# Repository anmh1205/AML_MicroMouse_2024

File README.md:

# AML MicroMouse 2024

A Micromouse robotics development repository combining STM32-based firmware variants, maze-solving algorithms, hardware design, simulation, and engineering records from the 2024 project.

## Project overview

Micromouse is a robotics challenge that combines mapping an unknown maze with planning and accurately driving a route to the destination. The 2024 project explores both sides of that problem: embedded-control software for the physical robot and software tools for developing and testing maze-solving behavior.

Unlike a single-board firmware example, this repository preserves **multiple hardware and firmware variants**, development experiments, technical references, and documentation. A directory name may refer to an earlier board revision rather than the final target.

## What is included

| Area | Examples found in the repository |
| --- | --- |
| Embedded firmware | STM32 projects, startup files, HAL drivers, MCU configurations |
| MCU variants | STM32F407-related projects and an STM32H743-based all-in-one board project |
| Real-time software | FreeRTOS experiments and related MCU project material |
| Navigation | Maze-solving and simulator-oriented development |
| Supporting devices | ESP32 screen and configuration-tool experiments |
| Hardware | PCB designs, drawings, and component references |
| Project records | Planning documents, calibration spreadsheets, and presentations |

The repository's `main` branch is an archival development snapshot. Individual board variants may require different MCU targets, clocks, pin assignments, and toolchains.

## Finding the correct firmware project

The main firmware workspace is under [`1. MicroMouse Code/`](1.%20MicroMouse%20Code/). For example:

- `2. MicroMouse - STM32F407VGT6/PCB_V1/` includes STM32 project files and an `.ioc` MCU configuration.
- `2. MicroMouse - STM32F407VGT6/PCB_AIO_V2_CODE/` includes a separate project configured for an STM32H743 device.
- `2. MicroMouse - STM32F407VGT6/FreeRTOS/` holds RTOS-related experiments.

Select a project **by the MCU and board configuration inside it**, not just by its parent folder name.

### Build workflow

1. Identify the matching PCB revision and microcontroller.
2. Open the relevant STM32CubeIDE/STM32CubeMX or CMake project according to the files in that variant.
3. Confirm the toolchain, generated configuration, linker script, libraries, and debugger interface.
4. Compile before connecting the physical robot; then verify pin mapping, sensor interfaces, and motor outputs before flashing.

Because the repository includes separate historical experiments and generated build artifacts, there is no single verified command that builds every directory.

## Repository guide

- [Examples and references](0.%20Example/) — datasheets, sample code, tool downloads, and experiments.
- [Firmware variants](1.%20MicroMouse%20Code/) — controller projects, ESP32-related code, and maze-solving work.
- [Electronics](2.%20MicroMouse%20PCB/) — PCB and supporting hardware files.
- [Drawings](3.%20Drawing/) — mechanical design materials.
- [Technical documentation](4.%20Document/) — reports, planning spreadsheets, and supporting materials.

## Relationship to the earlier project

[AML_MicroMouse](https://github.com/anmh1205/AML_MicroMouse) documents an earlier STM32F407VET6 Micromouse project, with competition footage and simulator materials. This repository preserves the 2024 development work and its additional hardware and firmware experiments.

## Scope and reuse

The included code and documents are engineering reference material, not a prepackaged firmware release. Third-party resources under the examples and simulator directories may have their own licenses. No repository-wide license is currently declared.

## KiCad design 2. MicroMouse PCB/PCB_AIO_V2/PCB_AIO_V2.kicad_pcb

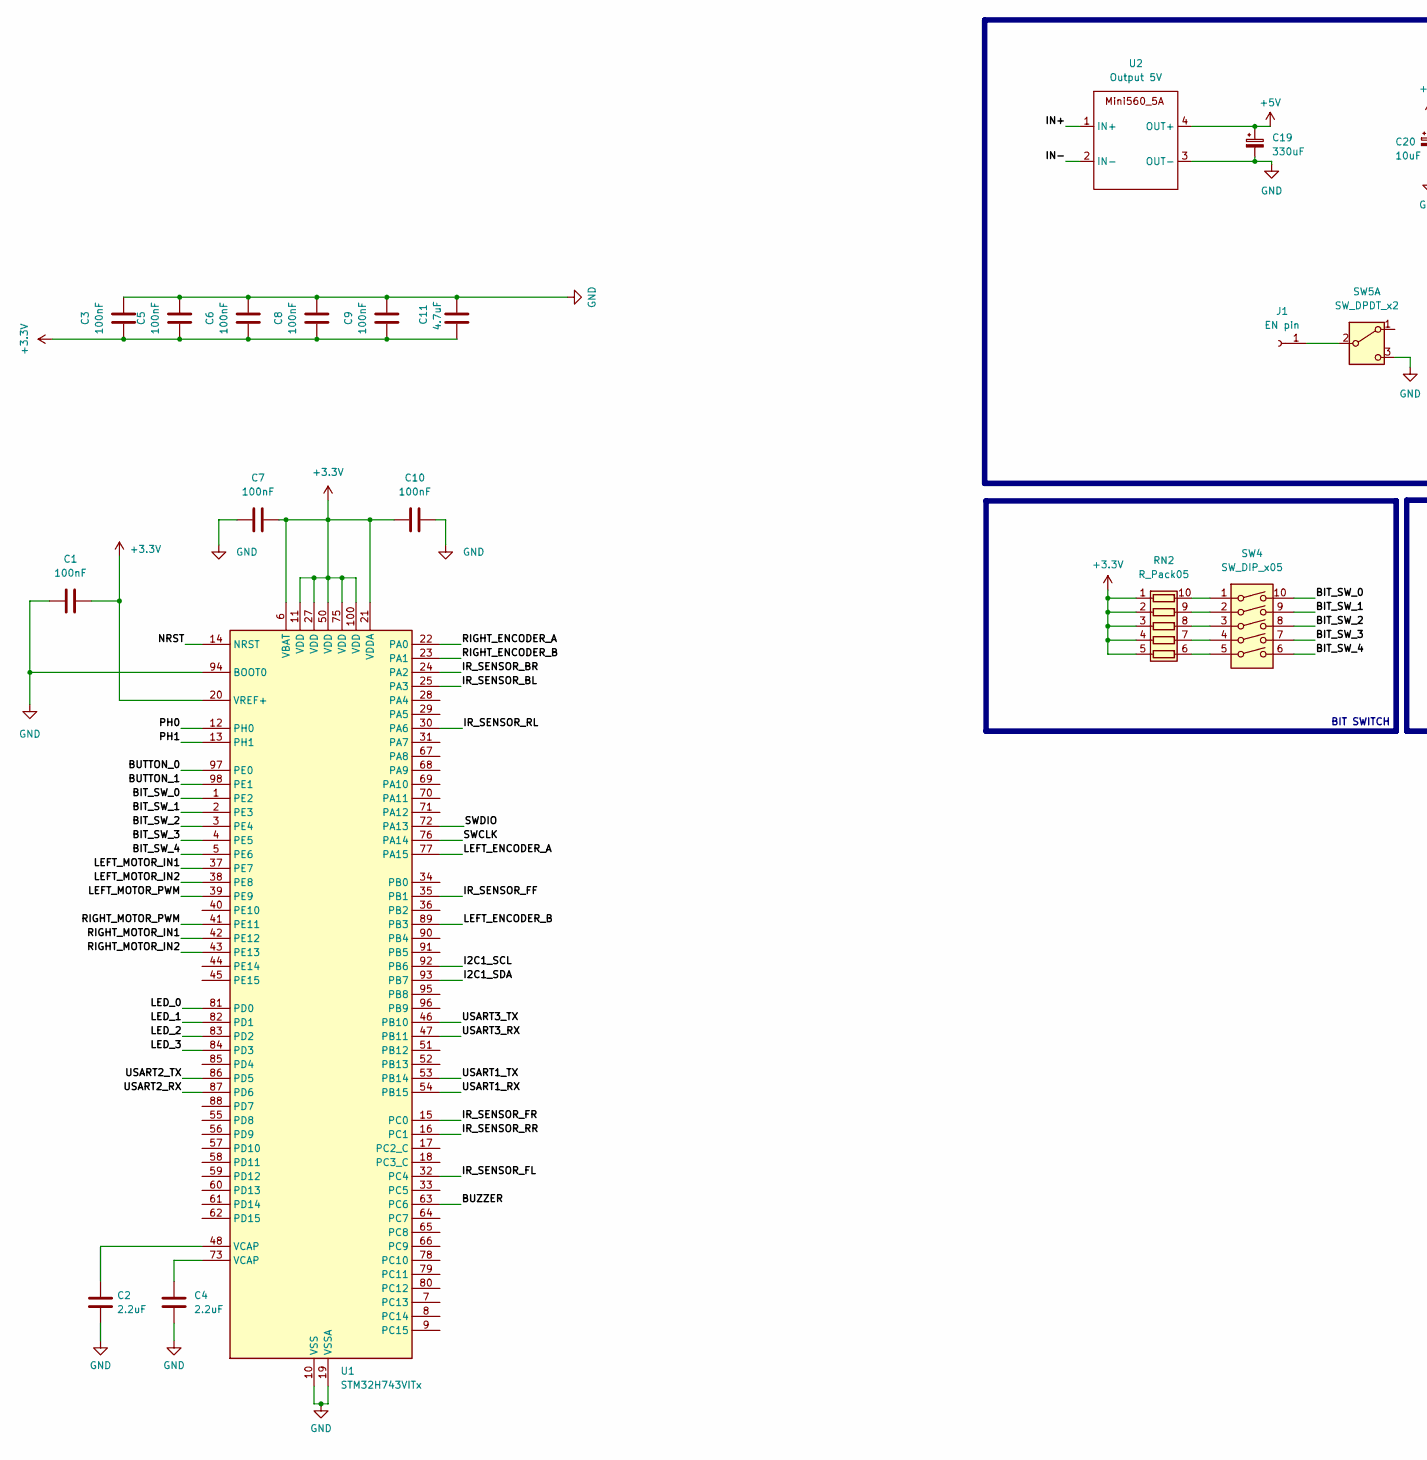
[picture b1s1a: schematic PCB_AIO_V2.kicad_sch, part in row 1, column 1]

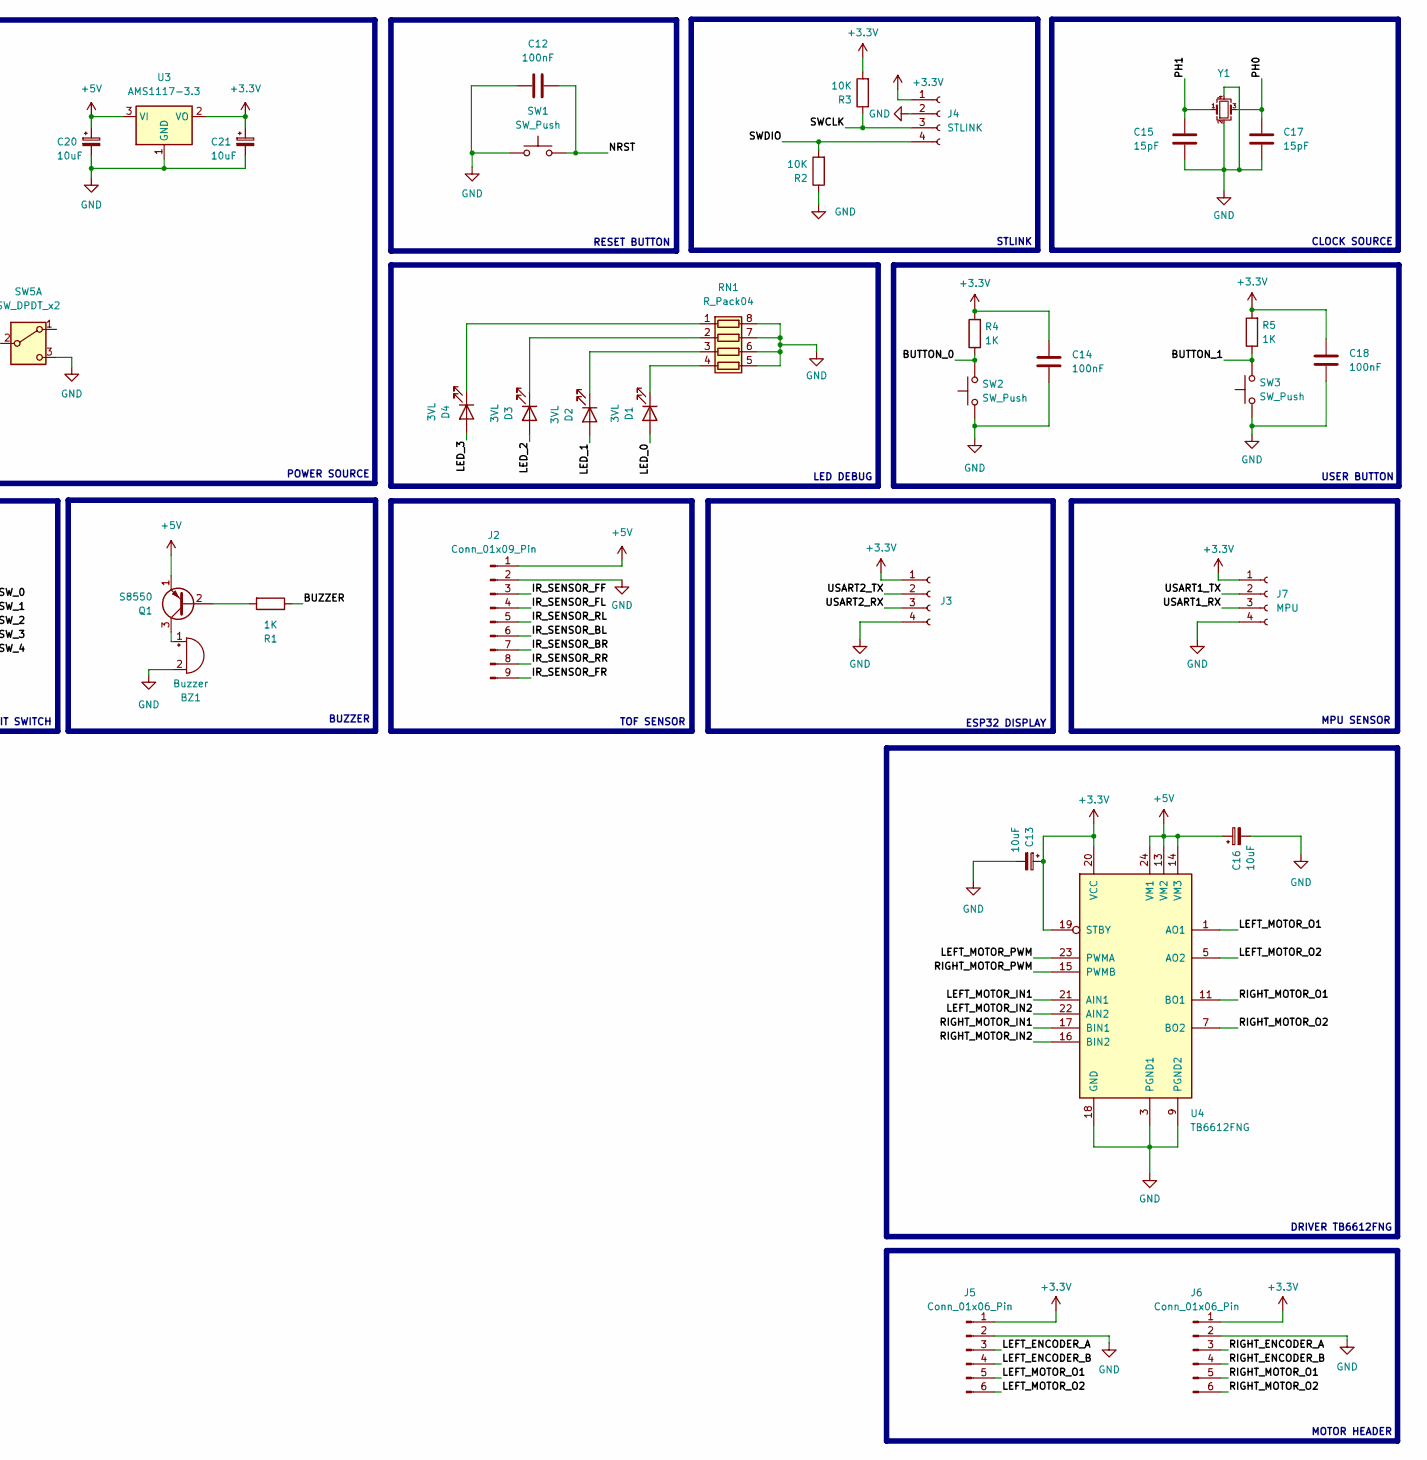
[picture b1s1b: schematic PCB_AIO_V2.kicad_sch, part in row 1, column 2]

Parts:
BZ1: Buzzer; MagneticBuzzer_CUI_CMT-8504-100-SMT
C1, C3, C5, C6, C7, C8, C9, C10, C12, C14, C18: 100nF; C_0603_1608Metric
C2, C4: 2.2uF; CP_EIA-3216-10_Kemet-I
C11: 4.7uF; CP_EIA-3216-10_Kemet-I
C13, C16: 10uF; C_0603_1608Metric
C15, C17: 15pF; C_0603_1608Metric
C19: 330uF; CP_EIA-7343-20_Kemet-V
C20, C21: 10uF; CP_EIA-3216-10_Kemet-I
D1, D2, D3, D4: 3VL; LED_0603_1608Metric
J1: EN pin; PinHeader_1x01_P2.54mm_Vertical
J2: Conn_01x09_Pin; PinHeader_1x09_P2.54mm_Vertical
J3: MPU; JST_SH_BM04B-SRSS-TB_1x04-1MP_P1.00mm_Vertical
J4: STLINK; JST_SH_BM04B-SRSS-TB_1x04-1MP_P1.00mm_Vertical
J5, J6: Conn_01x06_Pin; JST_SH_BM06B-SRSS-TB_1x06-1MP_P1.00mm_Vertical
J7: MPU; PinHeader_1x04_P2.54mm_Vertical
Q1: S8550; SOT-23
R1, R4, R5: 1K; R_0603_1608Metric
R2, R3: 10K; R_0603_1608Metric
RN1: R_Pack04; R_Array_Convex_4x0603
RN2: R_Pack05; R_Array_Convex_5x0603
SW1, SW2, SW3: SW_Push; SW_Tactile_SPST_NO_Straight_CK_PTS636Sx25SMTRLFS
SW4: SW_DIP_x05; SW_DIP_SPSTx05_Slide_KingTek_DSHP05TS_W7.62mm_P1.27mm
SW5: SW_DPDT_x2; SW_SPDT_PCM12
U1: STM32H743VITx; LQFP-100_14x14mm_P0.5mm
U2: Output 5V; Mini560_5A
U3: AMS1117-3.3; SOT-223-3_TabPin2
U4: TB6612FNG; SSOP-24_5.3x8.2mm_P0.65mm
Y1: Crystal_GND24_Small; Crystal_SMD_3225-4Pin_3.2x2.5mm

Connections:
+3.3V: C1.2, C3.1, C5.1, C6.1, C7.2, C8.1, C9.1, C10.1, C11.1, C13.1, C14.2, C18.2, C21.1, J3.1, J4.1, J5.1, J6.1, J7.1, R3.2, R4.2, R5.2, RN2.1 (R1.1), RN2.2 (R2.1), RN2.3 (R3.1), RN2.4 (R4.1), RN2.5 (R5.1), U1.6 (VBAT), U1.11 (VDD), U1.20 (VREF+), U1.21 (VDDA), U1.27 (VDD), U1.50 (VDD), U1.75 (VDD), U1.100 (VDD), U3.2 (VO), U4.19 (STBY), U4.20 (VCC)
+5V: C16.1, C19.1, C20.1, J2.1, Q1.1 (E), U2.4 (OUT+), U3.3 (VI), U4.13 (VM2), U4.14 (VM3), U4.24 (VM1)
/BIT_SW_0: SW4.10, U1.1 (PE2)
/BIT_SW_1: SW4.9, U1.2 (PE3)
/BIT_SW_2: SW4.8, U1.3 (PE4)
/BIT_SW_3: SW4.7, U1.4 (PE5)
/BIT_SW_4: SW4.6, U1.5 (PE6)
/BUTTON_0: R4.1, SW2.2, U1.97 (PE0)
/BUTTON_1: R5.1, SW3.2, U1.98 (PE1)
/BUZZER: R1.1, U1.63 (PC6)
/I2C1_SCL: U1.92 (PB6)
/I2C1_SDA: U1.93 (PB7)
/IN+: U2.1 (IN+)
/IN-: U2.2 (IN-)
/IR_SENSOR_BL: J2.6, U1.25 (PA3)
/IR_SENSOR_BR: J2.7, U1.24 (PA2)
/IR_SENSOR_FF: J2.3, U1.35 (PB1)
/IR_SENSOR_FL: J2.4, U1.32 (PC4)
/IR_SENSOR_FR: J2.9, U1.15 (PC0)
/IR_SENSOR_RL: J2.5, U1.30 (PA6)
/IR_SENSOR_RR: J2.8, U1.16 (PC1)
/LED_0: D1.2 (A), U1.81 (PD0)
/LED_1: D2.2 (A), U1.82 (PD1)
/LED_2: D3.2 (A), U1.83 (PD2)
/LED_3: D4.2 (A), U1.84 (PD3)
/LEFT_ENCODER_A: J5.3, U1.77 (PA15)
/LEFT_ENCODER_B: J5.4, U1.89 (PB3)
/LEFT_MOTOR_IN1: U1.37 (PE7), U4.21 (AIN1)
/LEFT_MOTOR_IN2: U1.38 (PE8), U4.22 (AIN2)
/LEFT_MOTOR_O1: J5.5, U4.1 (AO1), U4.2 (AO1)
/LEFT_MOTOR_O2: J5.6, U4.5 (AO2), U4.6 (AO2)
/LEFT_MOTOR_PWM: U1.39 (PE9), U4.23 (PWMA)
/NRST: C12.2, SW1.2, U1.14 (NRST)
/PH0: C17.2, U1.12 (PH0), Y1.3
/PH1: C15.2, U1.13 (PH1), Y1.1
/RIGHT_ENCODER_A: J6.3, U1.22 (PA0)
/RIGHT_ENCODER_B: J6.4, U1.23 (PA1)
/RIGHT_MOTOR_IN1: U1.42 (PE12), U4.17 (BIN1)
/RIGHT_MOTOR_IN2: U1.43 (PE13), U4.16 (BIN2)
/RIGHT_MOTOR_O1: J6.5, U4.11 (BO1), U4.12 (BO1)
/RIGHT_MOTOR_O2: J6.6, U4.7 (BO2), U4.8 (BO2)
/RIGHT_MOTOR_PWM: U1.41 (PE11), U4.15 (PWMB)
/SWCLK: J4.3, R3.1, U1.76 (PA14)
/SWDIO: J4.4, R2.2, U1.72 (PA13)
/USART1_RX: J7.3, U1.54 (PB15)
/USART1_TX: J7.2, U1.53 (PB14)
/USART2_RX: J3.3, U1.87 (PD6)
/USART2_TX: J3.2, U1.86 (PD5)
/USART3_RX: U1.47 (PB11)
/USART3_TX: U1.46 (PB10)
GND: BZ1.2 (+), C1.1, C2.1, C3.2, C4.1, C5.2, C6.2, C7.1, C8.2, C9.2, C10.2, C11.2, C12.1, C13.2, C14.1, C15.1, C16.2, C17.1, C18.1, C19.2, C20.2, C21.2, J2.2, J3.4, J4.2, J5.2, J6.2, J7.4, R2.1, RN1.5 (R4.2), RN1.6 (R3.2), RN1.7 (R2.2), RN1.8 (R1.2), SW1.1, SW2.1, SW3.1, SW5.3 (C), U1.10 (VSS), U1.19 (VSSA), U1.26 (VSS), U1.49 (VSS), U1.74 (VSS), U1.94 (BOOT0), U1.99 (VSS), U2.3 (OUT-), U3.1 (GND), U4.3 (PGND1), U4.4 (PGND1), U4.9 (PGND2), U4.10 (PGND2), U4.18 (GND), Y1.2, Y1.4
unnamed: BZ1.1 (-), Q1.3 (C)
unnamed: C2.2, U1.48 (VCAP)
unnamed: C4.2, U1.73 (VCAP)
unnamed: D1.1 (K), RN1.4 (R4.1)
unnamed: D2.1 (K), RN1.3 (R3.1)
unnamed: D3.1 (K), RN1.2 (R2.1)
unnamed: D4.1 (K), RN1.1 (R1.1)
unnamed: J1.1, SW5.2 (B)
unnamed: Q1.2 (B), R1.2
unnamed: RN2.10 (R1.2), SW4.1
unnamed: RN2.9 (R2.2), SW4.2
unnamed: RN2.8 (R3.2), SW4.3
unnamed: RN2.7 (R4.2), SW4.4
unnamed: RN2.6 (R5.2), SW4.5

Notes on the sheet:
DRIVER TB6612FNG
ESP32 DISPLAY
BIT SWITCH
BUZZER
RESET BUTTON
MPU SENSOR
POWER SOURCE
MOTOR HEADER
STLINK
TOF SENSOR
LED DEBUG
CLOCK SOURCE
USER BUTTON

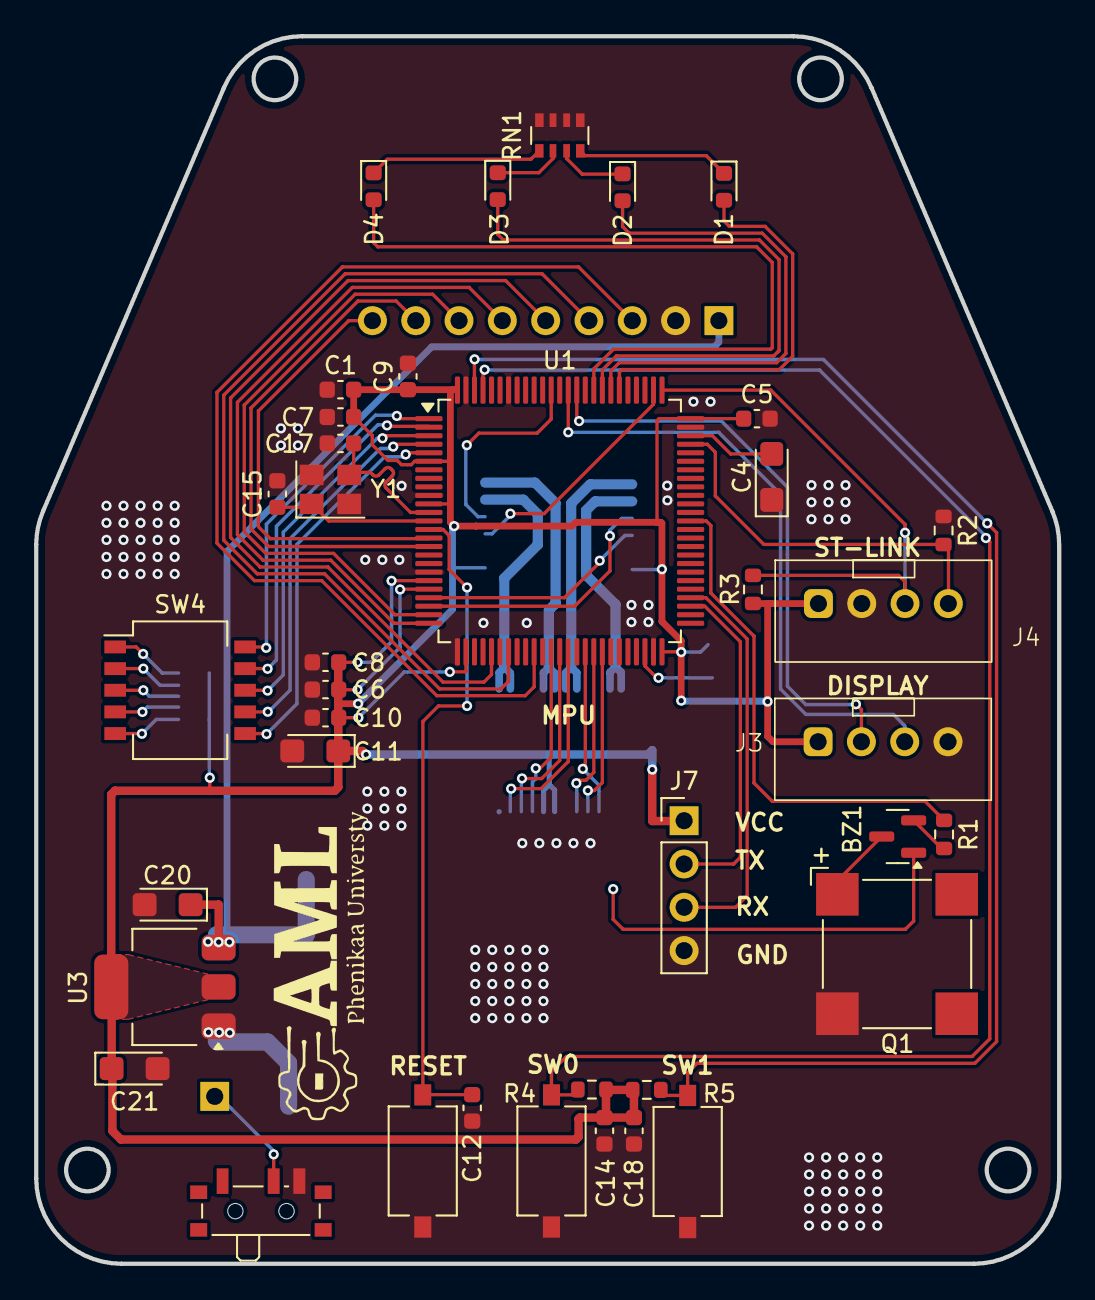
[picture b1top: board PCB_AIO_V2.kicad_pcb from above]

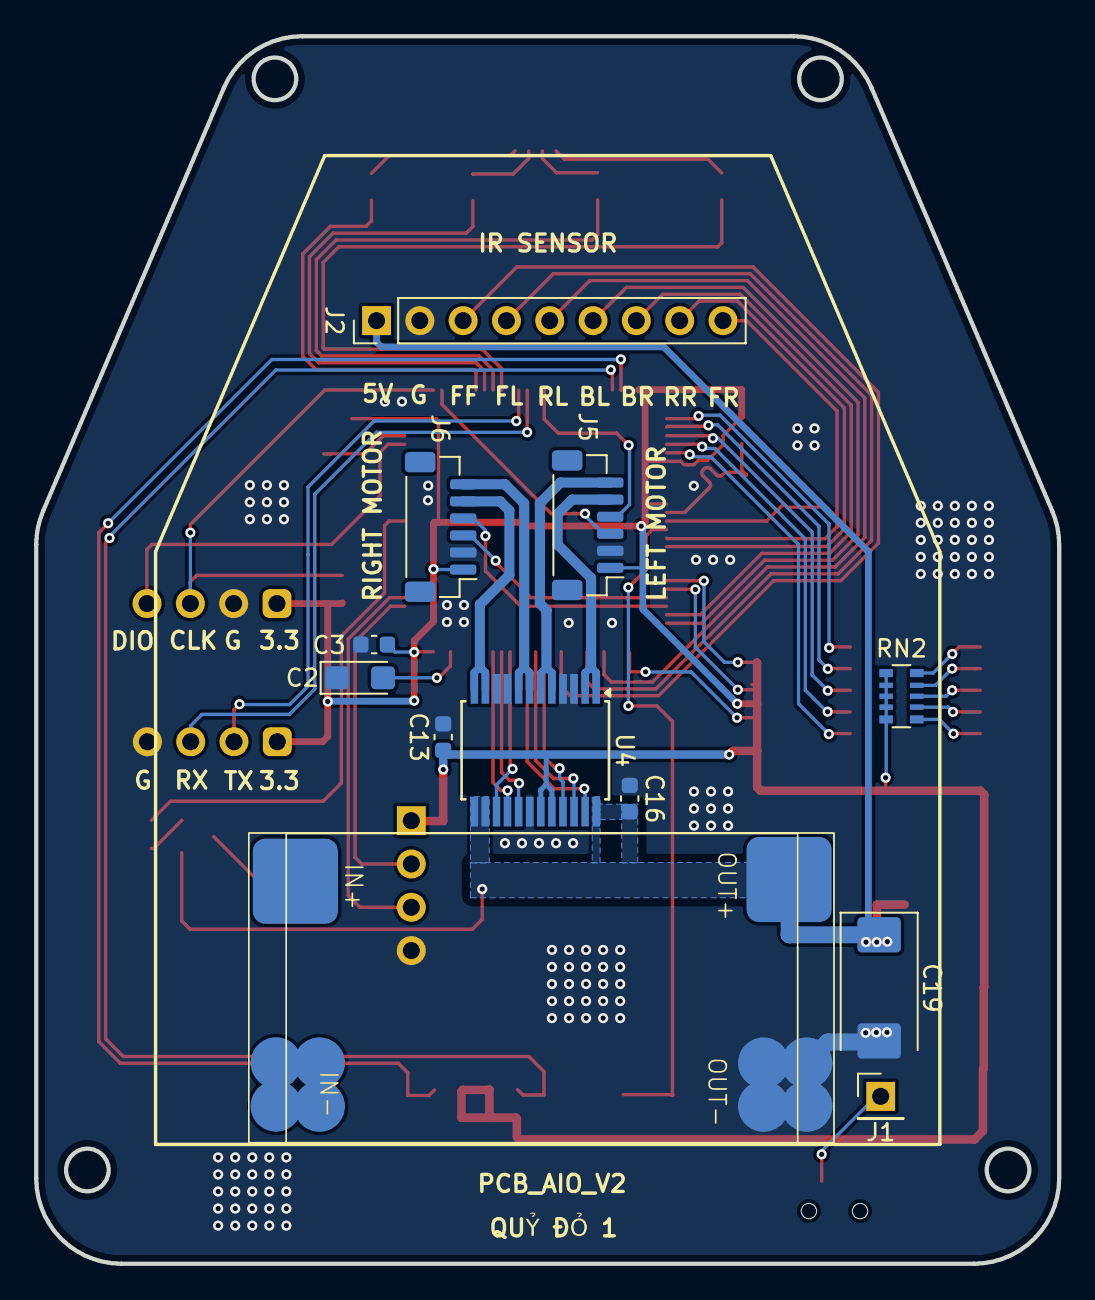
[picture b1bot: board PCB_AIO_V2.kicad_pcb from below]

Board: 2 copper layers, 60.0 x 72.0 mm, 51 parts (12 on the bottom side), 59 nets.

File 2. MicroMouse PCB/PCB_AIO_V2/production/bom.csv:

Designator,Footprint,Quantity,Value,LCSC Part #
BZ1,MagneticBuzzer_CUI_CMT-8504-100-SMT,1,Buzzer,
"C1, C10, C12, C14, C18, C3, C5, C6, C7, C8, C9",0603,11,100nF,
C11,CP_EIA-3216-10_Kemet-I,1,4.7uF,
"C13, C16",0603,2,10uF,
"C15, C17",0603,2,15pF,
C19,CP_EIA-7343-20_Kemet-V,1,330uF,
"C2, C4",CP_EIA-3216-10_Kemet-I,2,2.2uF,
"C20, C21",CP_EIA-3216-10_Kemet-I,2,10uF,
"D1, D2, D3, D4",0603,4,3VL,
J1,PinHeader_1x01_P2.54mm_Vertical,1,EN pin,
J2,PinHeader_1x09_P2.54mm_Vertical,1,Conn_01x09_Pin,
J3,JST_SH_BM04B-SRSS-TB_1x04-1MP_P1.00mm_Vertical,1,MPU,
J4,JST_SH_BM04B-SRSS-TB_1x04-1MP_P1.00mm_Vertical,1,STLINK,
"J5, J6",JST_SH_BM06B-SRSS-TB_1x06-1MP_P1.00mm_Vertical,2,Conn_01x06_Pin,
J7,PinHeader_1x04_P2.54mm_Vertical,1,MPU,
Q1,SOT-23,1,S8550,
"R1, R4, R5",0603,3,1K,
"R2, R3",0603,2,10K,
RN1,R_Array_Convex_4x0603,1,R_Pack04,
RN2,R_Array_Convex_5x0603,1,R_Pack05,
"SW1, SW2, SW3",SW_Tactile_SPST_NO_Straight_CK_PTS636Sx25SMTRLFS,3,SW_Push,
SW4,SW_DIP_SPSTx05_Slide_KingTek_DSHP05TS_W7.62mm_P1.27mm,1,SW_DIP_x05,
SW5,SW_SPDT_PCM12,1,SW_DPDT_x2,
U1,LQFP-100_14x14mm_P0.5mm,1,STM32H743VITx,
U2,Mini560_5A,1,Output 5V,
U3,SOT-223-3_TabPin2,1,AMS1117-3.3,
U4,SSOP-24_5.3x8.2mm_P0.65mm,1,TB6612FNG,
Y1,Crystal_SMD_3225-4Pin_3.2x2.5mm,1,Crystal_GND24_Small,

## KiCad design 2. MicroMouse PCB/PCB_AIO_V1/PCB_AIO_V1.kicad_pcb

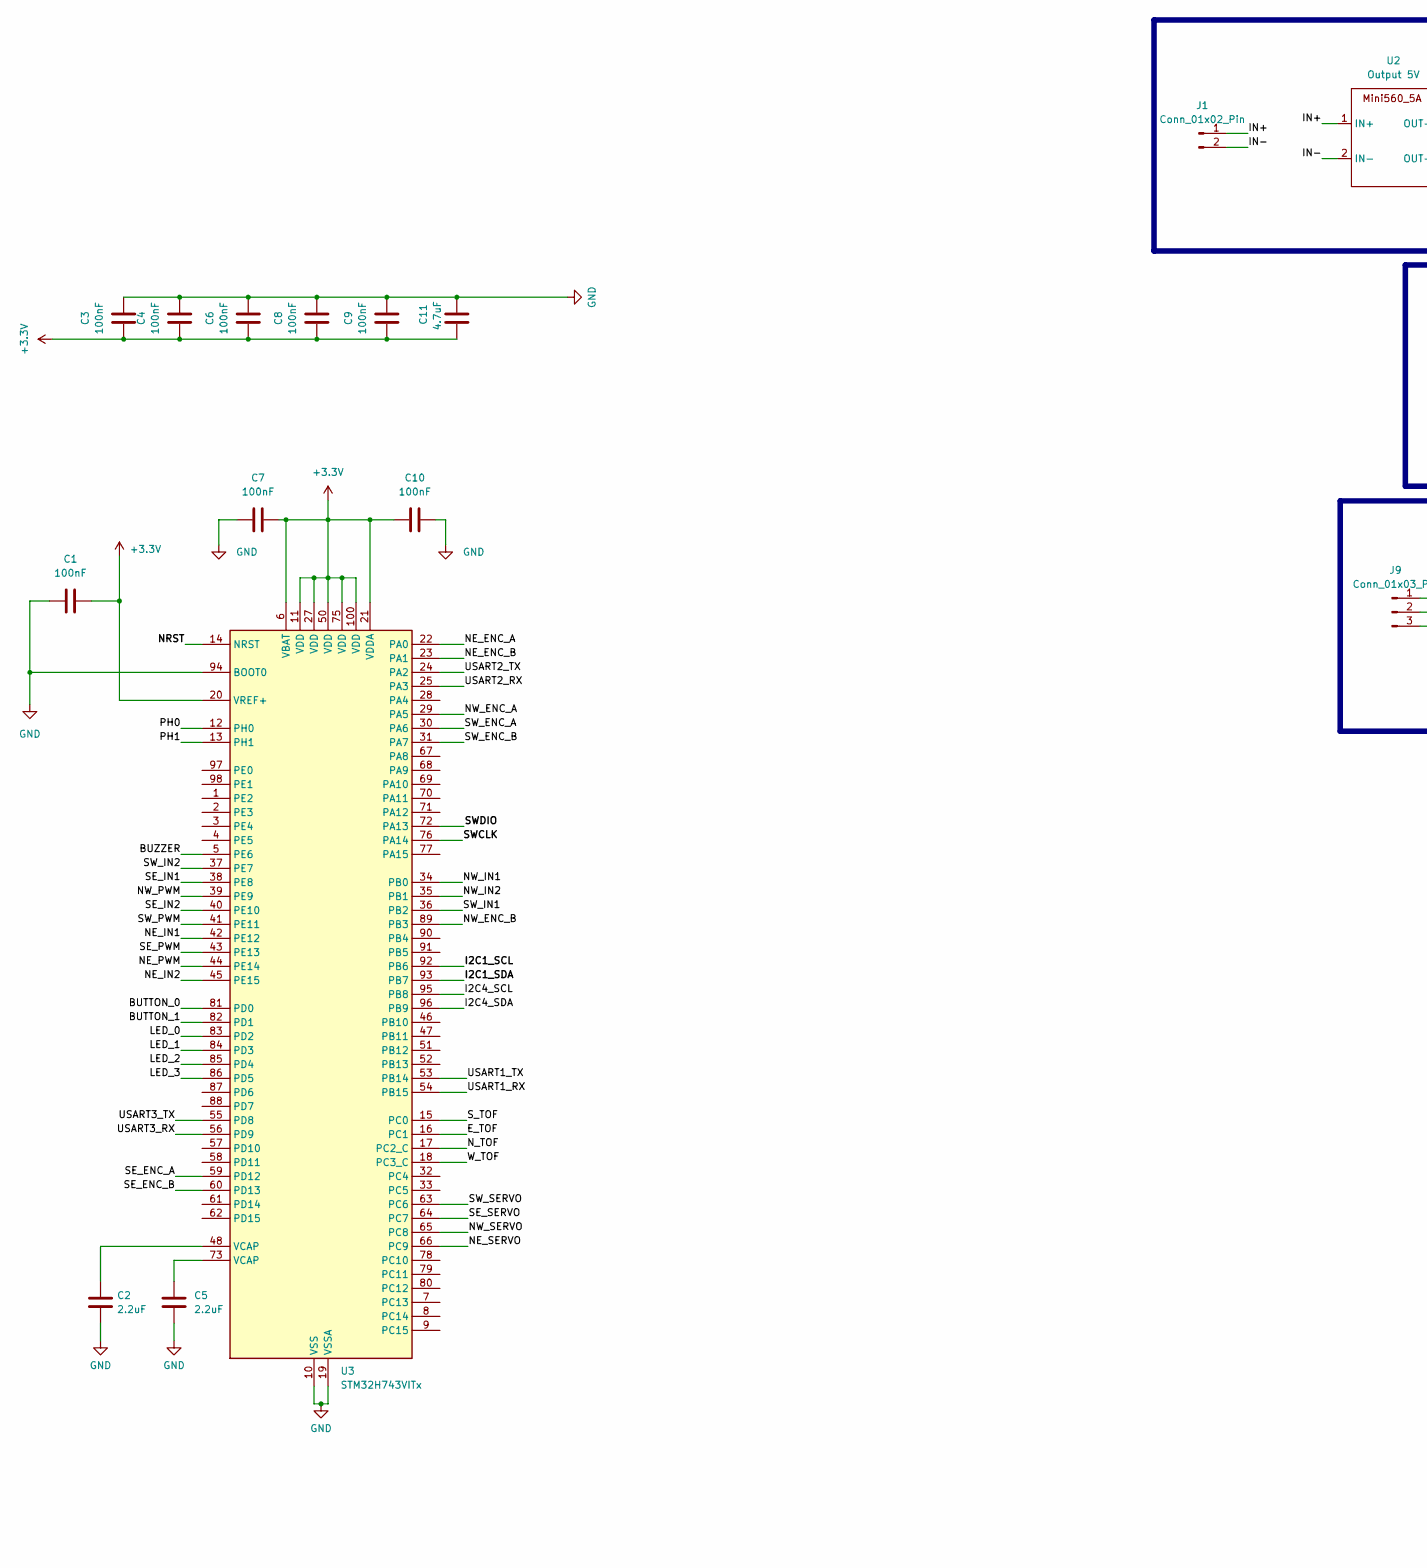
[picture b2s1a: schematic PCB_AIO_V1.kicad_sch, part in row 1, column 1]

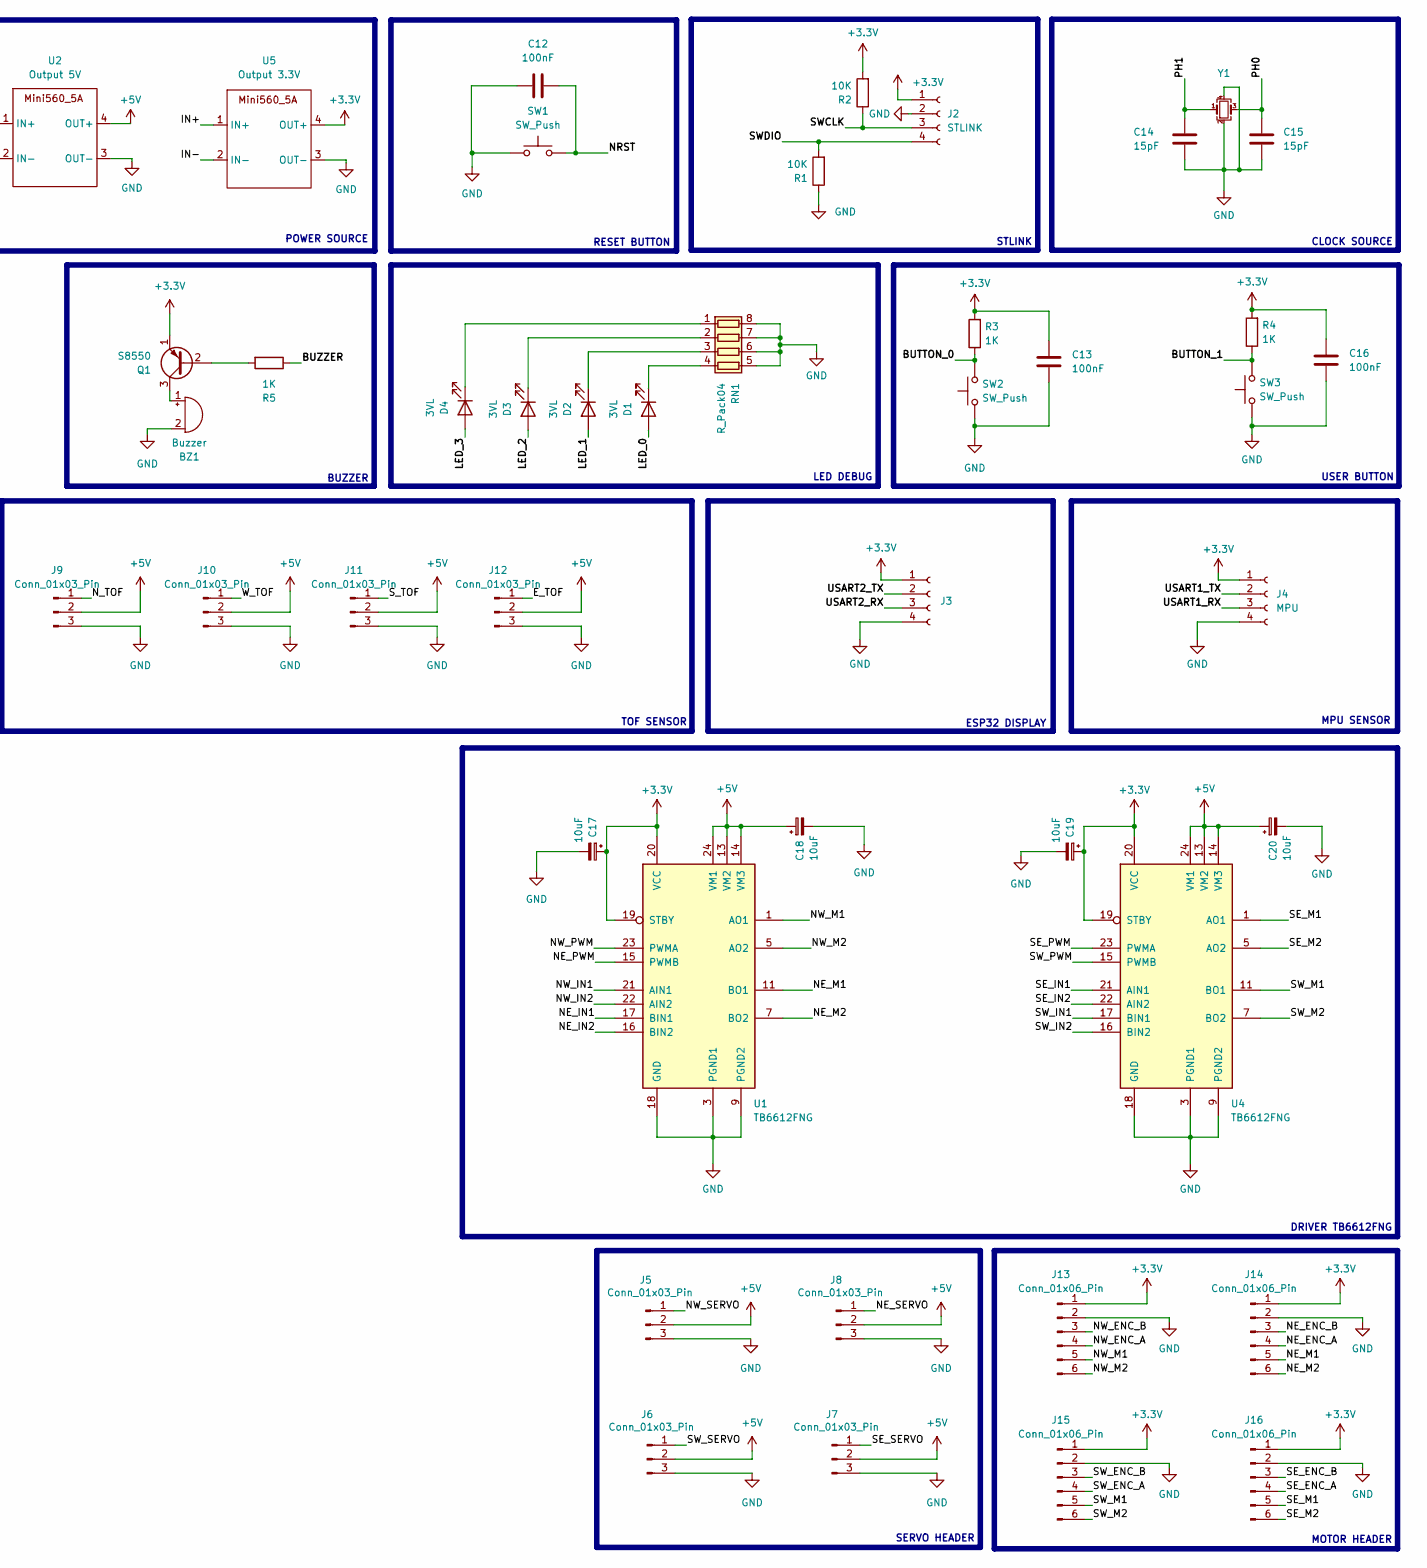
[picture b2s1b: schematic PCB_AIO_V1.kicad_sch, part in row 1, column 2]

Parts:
BZ1: Buzzer; MagneticBuzzer_CUI_CMT-8504-100-SMT
C1, C3, C4, C6, C7, C8, C9, C10, C12, C13, C16: 100nF; C_0402_1005Metric
C2, C5: 2.2uF; CP_EIA-3216-10_Kemet-I
C11: 4.7uF; CP_EIA-3216-10_Kemet-I
C14, C15: 15pF; C_0402_1005Metric
C17, C18, C19, C20: 10uF; C_0603_1608Metric
D1, D2, D3, D4: 3VL; LED_0603_1608Metric
J1: Conn_01x02_Pin; JST_VH_B2P-VH-B_1x02_P3.96mm_Vertical
J2: STLINK; JST_SH_BM04B-SRSS-TB_1x04-1MP_P1.00mm_Vertical
J3: MPU; JST_SH_BM04B-SRSS-TB_1x04-1MP_P1.00mm_Vertical
J4: MPU; PinHeader_1x04_P2.54mm_Vertical
J5, J6, J7, J8: Conn_01x03_Pin; JST_SH_BM03B-SRSS-TB_1x03-1MP_P1.00mm_Vertical
J9, J10, J11, J12: Conn_01x03_Pin; JST_SH_SM03B-SRSS-TB_1x03-1MP_P1.00mm_Horizontal
J13, J14, J15, J16: Conn_01x06_Pin; JST_GH_SM06B-GHS-TB_1x06-1MP_P1.25mm_Horizontal
Q1: S8550; SOT-23
R1, R2: 10K; R_0402_1005Metric
R3, R4, R5: 1K; R_0402_1005Metric
RN1: R_Pack04; R_Array_Convex_4x0603
SW1, SW2, SW3: SW_Push; SW_Tactile_SPST_NO_Straight_CK_PTS636Sx25SMTRLFS
U1, U4: TB6612FNG; SSOP-24_5.3x8.2mm_P0.65mm
U2: Output 5V; Mini560_5A
U3: STM32H743VITx; LQFP-100_14x14mm_P0.5mm
U5: Output 3.3V; Mini560_5A
Y1: Crystal_GND24_Small; Crystal_SMD_3225-4Pin_3.2x2.5mm

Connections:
+3.3V: C1.2, C3.1, C4.1, C6.1, C7.2, C8.1, C9.1, C10.1, C11.1, C13.2, C16.2, C17.1, C19.1, J2.1, J3.1, J4.1, J13.1, J14.1, J15.1, J16.1, Q1.1 (E), R2.2, R3.2, R4.2, U1.19 (STBY), U1.20 (VCC), U3.6 (VBAT), U3.11 (VDD), U3.20 (VREF+), U3.21 (VDDA), U3.27 (VDD), U3.50 (VDD), U3.75 (VDD), U3.100 (VDD), U4.19 (STBY), U4.20 (VCC), U5.4 (OUT+)
+5V: C18.1, C20.1, J5.2, J6.2, J7.2, J8.2, J9.2, J10.2, J11.2, J12.2, U1.13 (VM2), U1.14 (VM3), U1.24 (VM1), U2.4 (OUT+), U4.13 (VM2), U4.14 (VM3), U4.24 (VM1)
/BUTTON_0: R3.1, SW2.2, U3.81 (PD0)
/BUTTON_1: R4.1, SW3.2, U3.82 (PD1)
/BUZZER: R5.1, U3.5 (PE6)
/E_TOF: J12.1, U3.16 (PC1)
/I2C1_SCL: U3.92 (PB6)
/I2C1_SDA: U3.93 (PB7)
/I2C4_SCL: U3.95 (PB8)
/I2C4_SDA: U3.96 (PB9)
/IN+: J1.1, U2.1 (IN+), U5.1 (IN+)
/IN-: J1.2, U2.2 (IN-), U5.2 (IN-)
/LED_0: D1.2 (A), U3.83 (PD2)
/LED_1: D2.2 (A), U3.84 (PD3)
/LED_2: D3.2 (A), U3.85 (PD4)
/LED_3: D4.2 (A), U3.86 (PD5)
/NE_ENC_A: J14.4, U3.22 (PA0)
/NE_ENC_B: J14.3, U3.23 (PA1)
/NE_IN1: U1.17 (BIN1), U3.42 (PE12)
/NE_IN2: U1.16 (BIN2), U3.45 (PE15)
/NE_M1: J14.5, U1.11 (BO1), U1.12 (BO1)
/NE_M2: J14.6, U1.7 (BO2), U1.8 (BO2)
/NE_PWM: U1.15 (PWMB), U3.44 (PE14)
/NE_SERVO: J8.1, U3.66 (PC9)
/NRST: C12.2, SW1.2, U3.14 (NRST)
/NW_ENC_A: J13.4, U3.29 (PA5)
/NW_ENC_B: J13.3, U3.89 (PB3)
/NW_IN1: U1.21 (AIN1), U3.34 (PB0)
/NW_IN2: U1.22 (AIN2), U3.35 (PB1)
/NW_M1: J13.5, U1.1 (AO1), U1.2 (AO1)
/NW_M2: J13.6, U1.5 (AO2), U1.6 (AO2)
/NW_PWM: U1.23 (PWMA), U3.39 (PE9)
/NW_SERVO: J5.1, U3.65 (PC8)
/N_TOF: J9.1, U3.17 (PC2_C)
/PH0: C15.2, U3.12 (PH0), Y1.3
/PH1: C14.2, U3.13 (PH1), Y1.1
/SE_ENC_A: J16.4, U3.59 (PD12)
/SE_ENC_B: J16.3, U3.60 (PD13)
/SE_IN1: U3.38 (PE8), U4.21 (AIN1)
/SE_IN2: U3.40 (PE10), U4.22 (AIN2)
/SE_M1: J16.5, U4.1 (AO1), U4.2 (AO1)
/SE_M2: J16.6, U4.5 (AO2), U4.6 (AO2)
/SE_PWM: U3.43 (PE13), U4.23 (PWMA)
/SE_SERVO: J7.1, U3.64 (PC7)
/SWCLK: J2.3, R2.1, U3.76 (PA14)
/SWDIO: J2.4, R1.2, U3.72 (PA13)
/SW_ENC_A: J15.4, U3.30 (PA6)
/SW_ENC_B: J15.3, U3.31 (PA7)
/SW_IN1: U3.36 (PB2), U4.17 (BIN1)
/SW_IN2: U3.37 (PE7), U4.16 (BIN2)
/SW_M1: J15.5, U4.11 (BO1), U4.12 (BO1)
/SW_M2: J15.6, U4.7 (BO2), U4.8 (BO2)
/SW_PWM: U3.41 (PE11), U4.15 (PWMB)
/SW_SERVO: J6.1, U3.63 (PC6)
/S_TOF: J11.1, U3.15 (PC0)
/USART1_RX: J4.3, U3.54 (PB15)
/USART1_TX: J4.2, U3.53 (PB14)
/USART2_RX: J3.3, U3.25 (PA3)
/USART2_TX: J3.2, U3.24 (PA2)
/USART3_RX: U3.56 (PD9)
/USART3_TX: U3.55 (PD8)
/W_TOF: J10.1, U3.18 (PC3_C)
GND: BZ1.2 (+), C1.1, C2.1, C3.2, C4.2, C5.1, C6.2, C7.1, C8.2, C9.2, C10.2, C11.2, C12.1, C13.1, C14.1, C15.1, C16.1, C17.2, C18.2, C19.2, C20.2, J2.2, J3.4, J4.4, J5.3, J6.3, J7.3, J8.3, J9.3, J10.3, J11.3, J12.3, J13.2, J14.2, J15.2, J16.2, R1.1, RN1.5 (R4.2), RN1.6 (R3.2), RN1.7 (R2.2), RN1.8 (R1.2), SW1.1, SW2.1, SW3.1, U1.3 (PGND1), U1.4 (PGND1), U1.9 (PGND2), U1.10 (PGND2), U1.18 (GND), U2.3 (OUT-), U3.10 (VSS), U3.19 (VSSA), U3.26 (VSS), U3.49 (VSS), U3.74 (VSS), U3.94 (BOOT0), U3.99 (VSS), U4.3 (PGND1), U4.4 (PGND1), U4.9 (PGND2), U4.10 (PGND2), U4.18 (GND), U5.3 (OUT-), Y1.2, Y1.4
unnamed: BZ1.1 (-), Q1.3 (C)
unnamed: C2.2, U3.48 (VCAP)
unnamed: C5.2, U3.73 (VCAP)
unnamed: D1.1 (K), RN1.4 (R4.1)
unnamed: D2.1 (K), RN1.3 (R3.1)
unnamed: D3.1 (K), RN1.2 (R2.1)
unnamed: D4.1 (K), RN1.1 (R1.1)
unnamed: Q1.2 (B), R5.2

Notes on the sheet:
LED DEBUG
SERVO HEADER
USER BUTTON
BUZZER
RESET BUTTON
POWER SOURCE
MOTOR HEADER
STLINK
ESP32 DISPLAY
DRIVER TB6612FNG
MPU SENSOR
CLOCK SOURCE
TOF SENSOR
